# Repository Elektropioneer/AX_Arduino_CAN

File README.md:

# AX_Arduino_CAN
Driver for Arduino Nano to control AX.
Communication protocol is CAN to connect it to our robot communication system. 
There are pinouts for I2C to easily connect Arduino supported sensors.

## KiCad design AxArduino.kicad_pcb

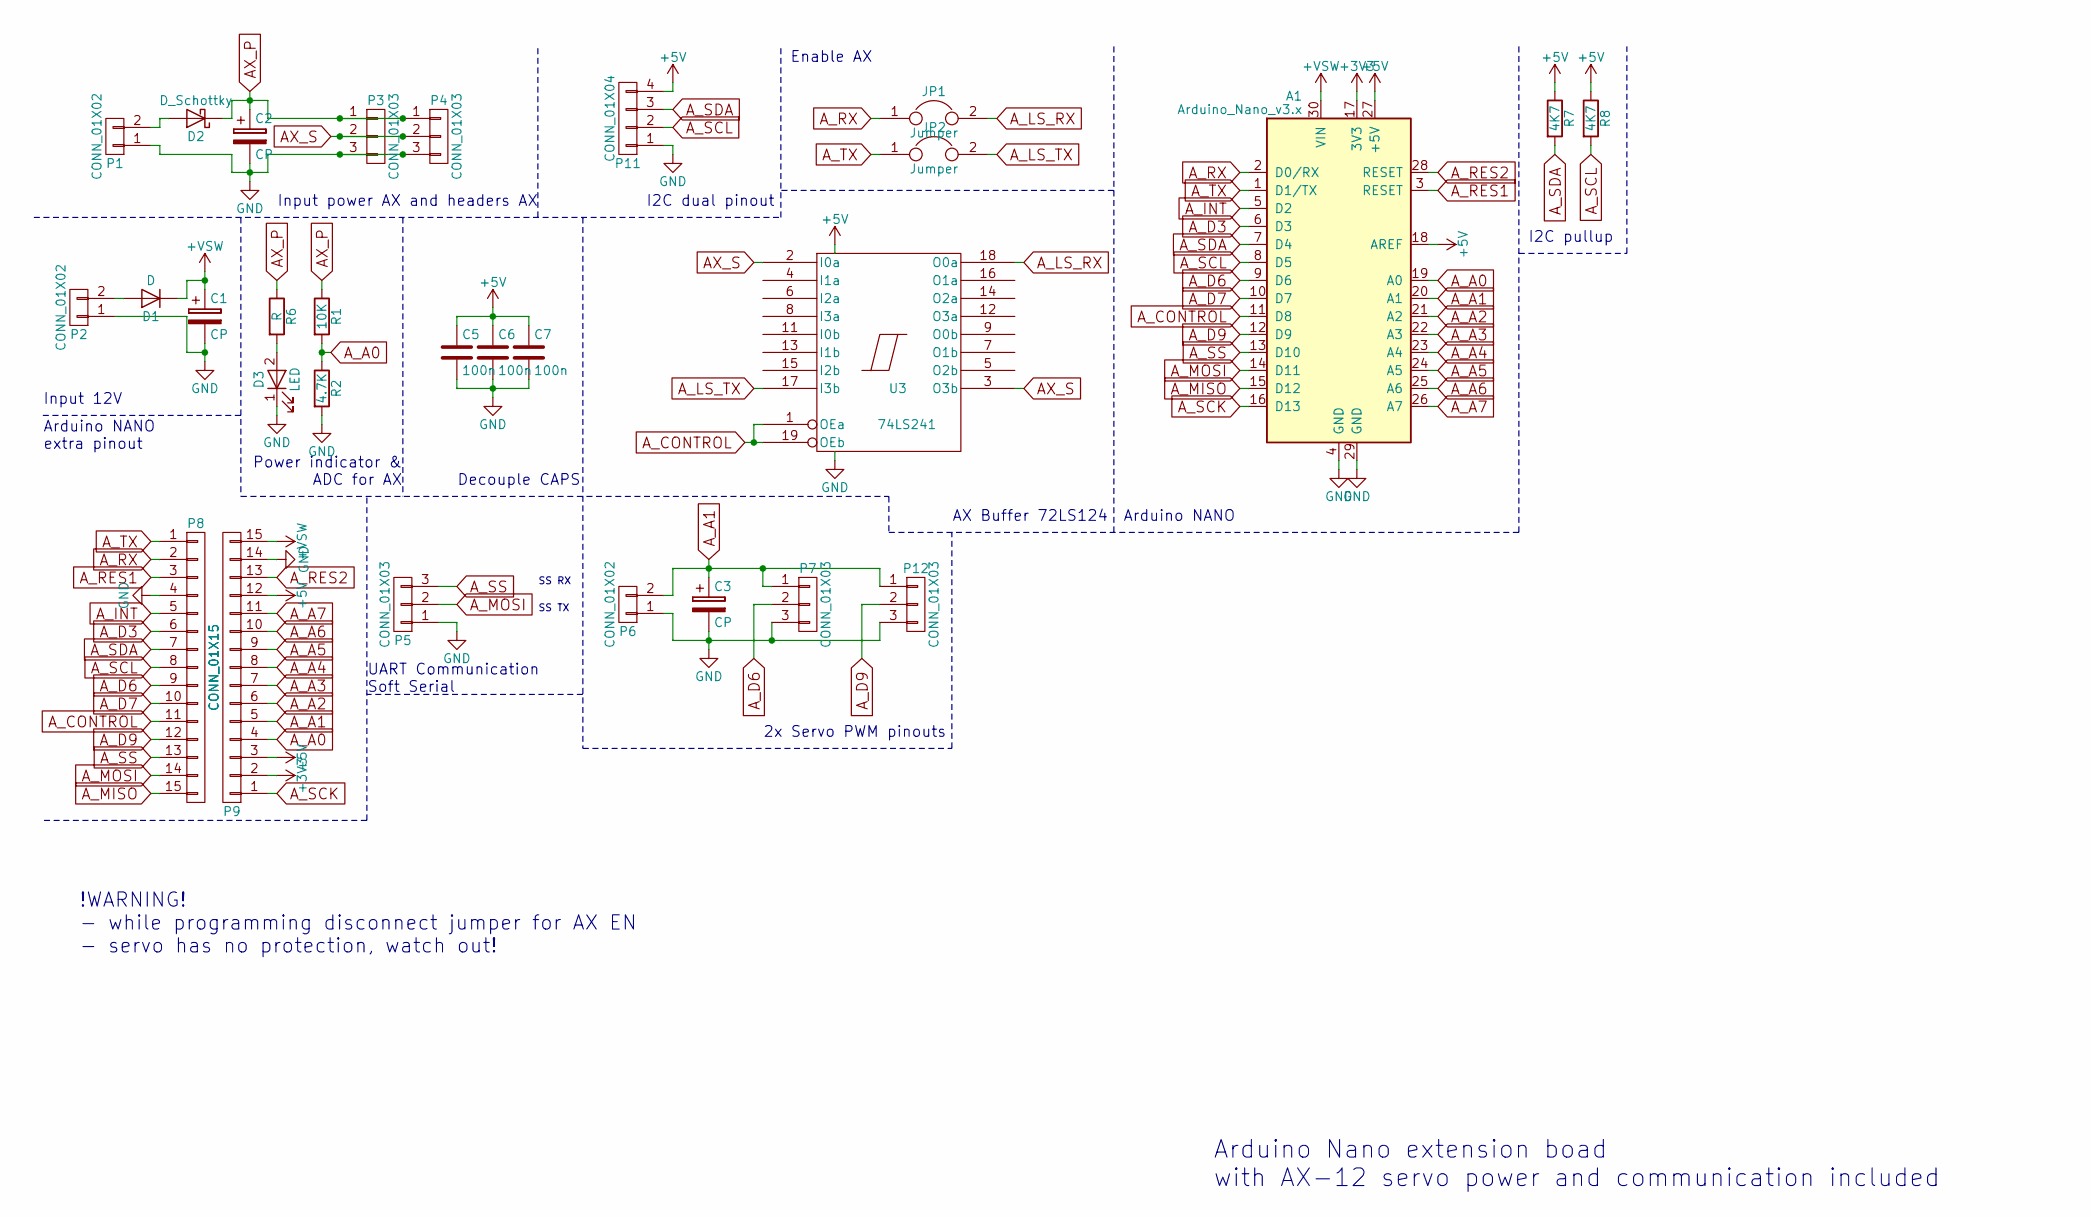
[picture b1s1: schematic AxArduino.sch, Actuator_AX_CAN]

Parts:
A1: Arduino_Nano_v3.x; Arduino_Nano_WithMountingHoles
C1, C2, C3: CP; CP_Elec_6.3x5.3
C5, C6, C7: 100n; C_0805
D1: D; Diode_DO-41_SOD81_Vertical_AnodeUp
D2: D_Schottky; SMB_Standard
D3: LED; LED_0805
JP1, JP2: Jumper; Pin_Header_Straight_1x02_Pitch2.54mm
P1, P2, P6: CONN_01X02; TerminalBlock_Pheonix_MKDS1.5-2pol
P3, P4, P5, P7, P12: CONN_01X03; Pin_Header_Straight_1x03_Pitch2.54mm
P8, P9: CONN_01X15; Pin_Header_Straight_1x15_Pitch2.54mm
P11: CONN_01X04; Pin_Header_Straight_1x04_Pitch2.54mm
R1: 10K; R_0805
R2: 4.7K; R_0805
R6: R; R_0805
R7, R8: 4K7; R_0805
U3: 74LS241; DIP-20_W7.62mm

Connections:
+3V3: A1.17 (3V3), P9.2
+5V: A1.18 (AREF), A1.27 (+5V), C5.1, C6.1, C7.1, P9.3, P9.12, P11.4, R7.1, R8.1, U3.20 (VCC)
+VSW: A1.30 (VIN), C1.1, D1.1 (K), P9.15
AX_P: C2.1, D2.1 (K), P3.1, P4.1, R1.1, R6.1
AX_S: P3.2, P4.2, U3.2 (I0a), U3.3 (O3b)
A_A0: A1.19 (A0), P9.4, R1.2, R2.1
A_A2: A1.21 (A2), P9.6
A_A3: A1.22 (A3), P9.7
A_A4: A1.23 (A4), P9.8
A_A5: A1.24 (A5), P9.9
A_A6: A1.25 (A6), P9.10
A_A7: A1.26 (A7), P9.11
A_CONTROL: A1.11 (D8), P8.11, U3.1 (OEa), U3.19 (OEb)
A_D3: A1.6 (D3), P8.6; also elsewhere on the board
A_D6: A1.9 (D6), P7.2, P8.9
A_D7: A1.10 (D7), P8.10; also elsewhere on the board
A_D9: A1.12 (D9), P8.12, P12.2
A_INT: A1.5 (D2), P8.5
A_LS_RX: JP1.2, U3.18 (O0a)
A_LS_TX: JP2.2, U3.17 (I3b)
A_MISO: A1.15 (D12), P8.15
A_MOSI: A1.14 (D11), P5.2, P8.14
A_RES1: A1.3 (RESET), P8.3
A_RES2: A1.28 (RESET), P9.13
A_RX: A1.2 (D0/RX), JP1.1, P8.2
A_SCK: A1.16 (D13), P9.1
A_SCL: A1.8 (D5), P8.8, P11.2, R8.2
A_SDA: A1.7 (D4), P8.7, P11.3, R7.2
A_SS: A1.13 (D10), P5.3, P8.13
A_TX: A1.1 (D1/TX), JP2.1, P8.1
GND: A1.4 (GND), A1.29 (GND), C1.2, C2.2, C3.2, C5.2, C6.2, C7.2, D3.1 (K), P1.1, P2.1, P3.3, P4.3, P5.1, P6.1, P7.3, P8.4, P9.14, P11.1, P12.3, R2.2, U3.10 (GND); also elsewhere on the board
unnamed: D1.2 (A), P2.2
unnamed: D2.2 (A), P1.2
unnamed: D3.2 (A), R6.2

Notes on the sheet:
Input power AX and headers AX
I2C dual pinout
AX Buffer 72LS124
Decouple CAPS
Power indicator & ADC for AX
Input 12V
Arduino NANO
Arduino NANO extra pinout
Enable AX
I2C pullup
SS RX
SS TX
2x Servo PWM pinouts
UART Communication Soft Serial
Arduino Nano extension boad with AX-12 servo power and communication included
!WARNING! - while programming disconnect jumper for AX EN - servo has no protection, watch out!

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
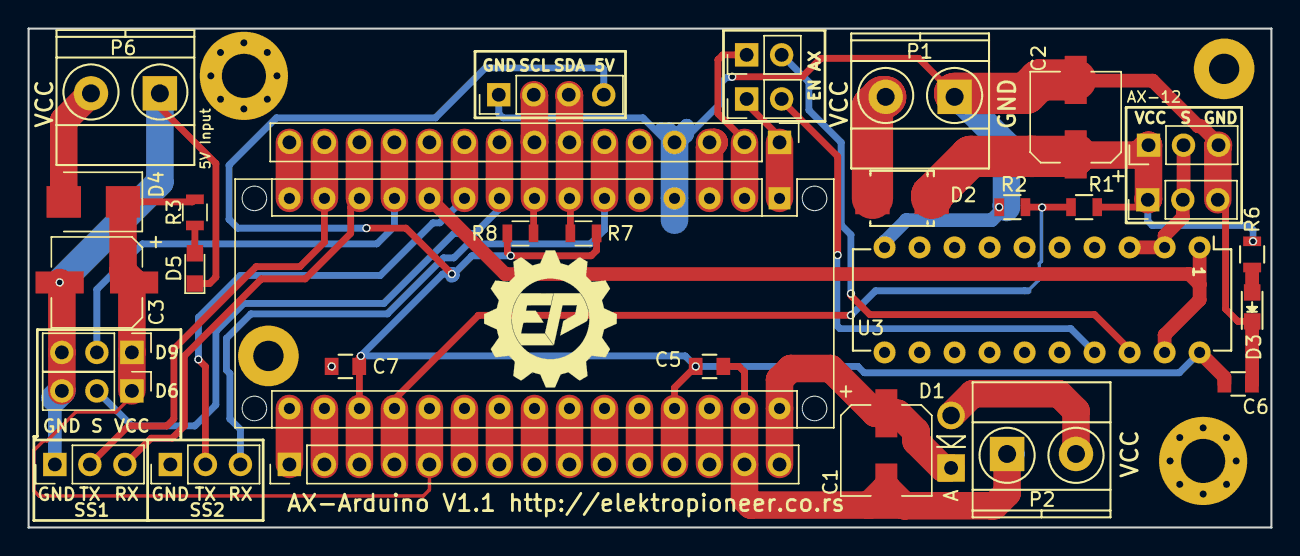
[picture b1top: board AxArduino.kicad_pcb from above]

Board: 2 copper layers, 90.2 x 36.2 mm, 37 parts (0 on the bottom side), 37 nets.

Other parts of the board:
D4: D_Schottky; D_SMB_Standard
D5: LED; LED_0805
MK1, MK2: Mounting_Hole; MountingHole_3.2mm_M3_Pad_Via
MK3, MK4: Mounting_Hole; MountingHole_2.2mm_M2_Pad
P10: CONN_01X03; Pin_Header_Straight_1x03_Pitch2.54mm
R3: R; R_0805

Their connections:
A_D3: P10.3; also elsewhere on the board
A_D7: P10.2; also elsewhere on the board
GND: D5.1, P10.1; also elsewhere on the board
unnamed: D5.2, R3.2

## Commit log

2017-11-19 Modif to readme
2017-11-23 Fixed stuff, like moving r to top layer and adding pullups to i2c
2017-12-31 New design
2018-02-10 Small modifs, added connectors and servo support
2018-02-10 Added pdf and images
2018-02-14 Issue: keep out
2018-02-26 Added gerber files
2018-02-26 Files updated, added mask
2018-04-02 halfway there ?
2018-04-03 Added actuator support, needs testing
2018-04-03 Additions
2018-04-05 Working with software serial
